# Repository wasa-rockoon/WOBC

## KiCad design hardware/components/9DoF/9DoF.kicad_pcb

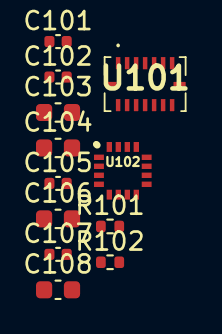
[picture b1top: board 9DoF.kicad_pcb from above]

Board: 2 copper layers, 12 parts (0 on the bottom side), 9 nets, no tracks yet.

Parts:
C101, C102, C107: 100nF; C_0402_1005Metric
C103, C104, C108: 10μF; C_0603_1608Metric
C105: 0.22μF; C_0402_1005Metric
C106: 4.7μF; C_0603_1608Metric
R101, R102: 4.7K; R_0402_1005Metric
U101: BMI088
U102: QMC5883L; _HMC5883L

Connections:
3V3: C101.1, C102.1, C103.1, C104.1, C107.1, C108.1, R101.2, R102.2, U101.3 (VDD), U101.7 (PS), U101.11 (VDDIO), U102.2 (VDD), U102.4 (S1), U102.13 (VDDIO)
AD0: R101.1, U101.15 (SDO1)
AD1: R102.1, U101.10 (SDO2)
GND: C101.2, C102.2, C103.2, C104.2, C106.2, C107.2, C108.2, U101.4 (GNDA), U101.6 (GNDIO), U102.9 (GND), U102.11 (GND)
unnamed: C106.1, U102.10 (C1)
unnamed: C105.1, U102.12 (SETC)
unnamed: C105.2, U102.8 (STEP)
SCL: U101.8 (SCL/SCK), U102.1 (SCL)
SDA: U101.9 (SDA/SDI), U102.16 (SDA)

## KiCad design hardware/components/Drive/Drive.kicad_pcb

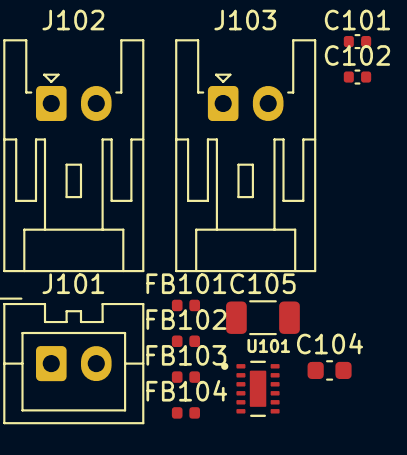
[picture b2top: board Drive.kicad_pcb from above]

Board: 2 copper layers, 12 parts (0 on the bottom side), 11 nets, no tracks yet.

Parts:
C101, C102: 100n; C_0402_1005Metric
C104: 10u; C_0603_1608Metric
C105: 100u; C_1206_3216Metric
FB101, FB102, FB103, FB104: FerriteBead; L_0402_1005Metric
J101: Conn_01x02_Pin; JST_XA_B02B-XASK-1_1x02_P2.50mm_Vertical
J102, J103: Conn_01x02_Pin; JST_XA_S02B-XASK-1N-BN_1x02_P2.50mm_Horizontal
U101: SON50P300X200X80-13N

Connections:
/VDD: C102.1, U101.12 (VCC)
AOUT1: FB101.1, U101.2 (AOUT1)
AOUT2: FB102.1, U101.3 (AOUT2)
BOUT1: FB103.1, U101.4 (BOUT1)
BOUT2: FB104.1, U101.5 (BOUT2)
GND: C101.2, C102.2, C104.2, C105.2, J101.2, U101.6 (GND), U101.11 (MODE), U101.13 (GND)
unnamed: C101.1, C104.1, C105.1, J101.1, U101.1 (VM)
unnamed: FB101.2, J102.1
unnamed: FB102.2, J102.2
unnamed: FB103.2, J103.1
unnamed: FB104.2, J103.2

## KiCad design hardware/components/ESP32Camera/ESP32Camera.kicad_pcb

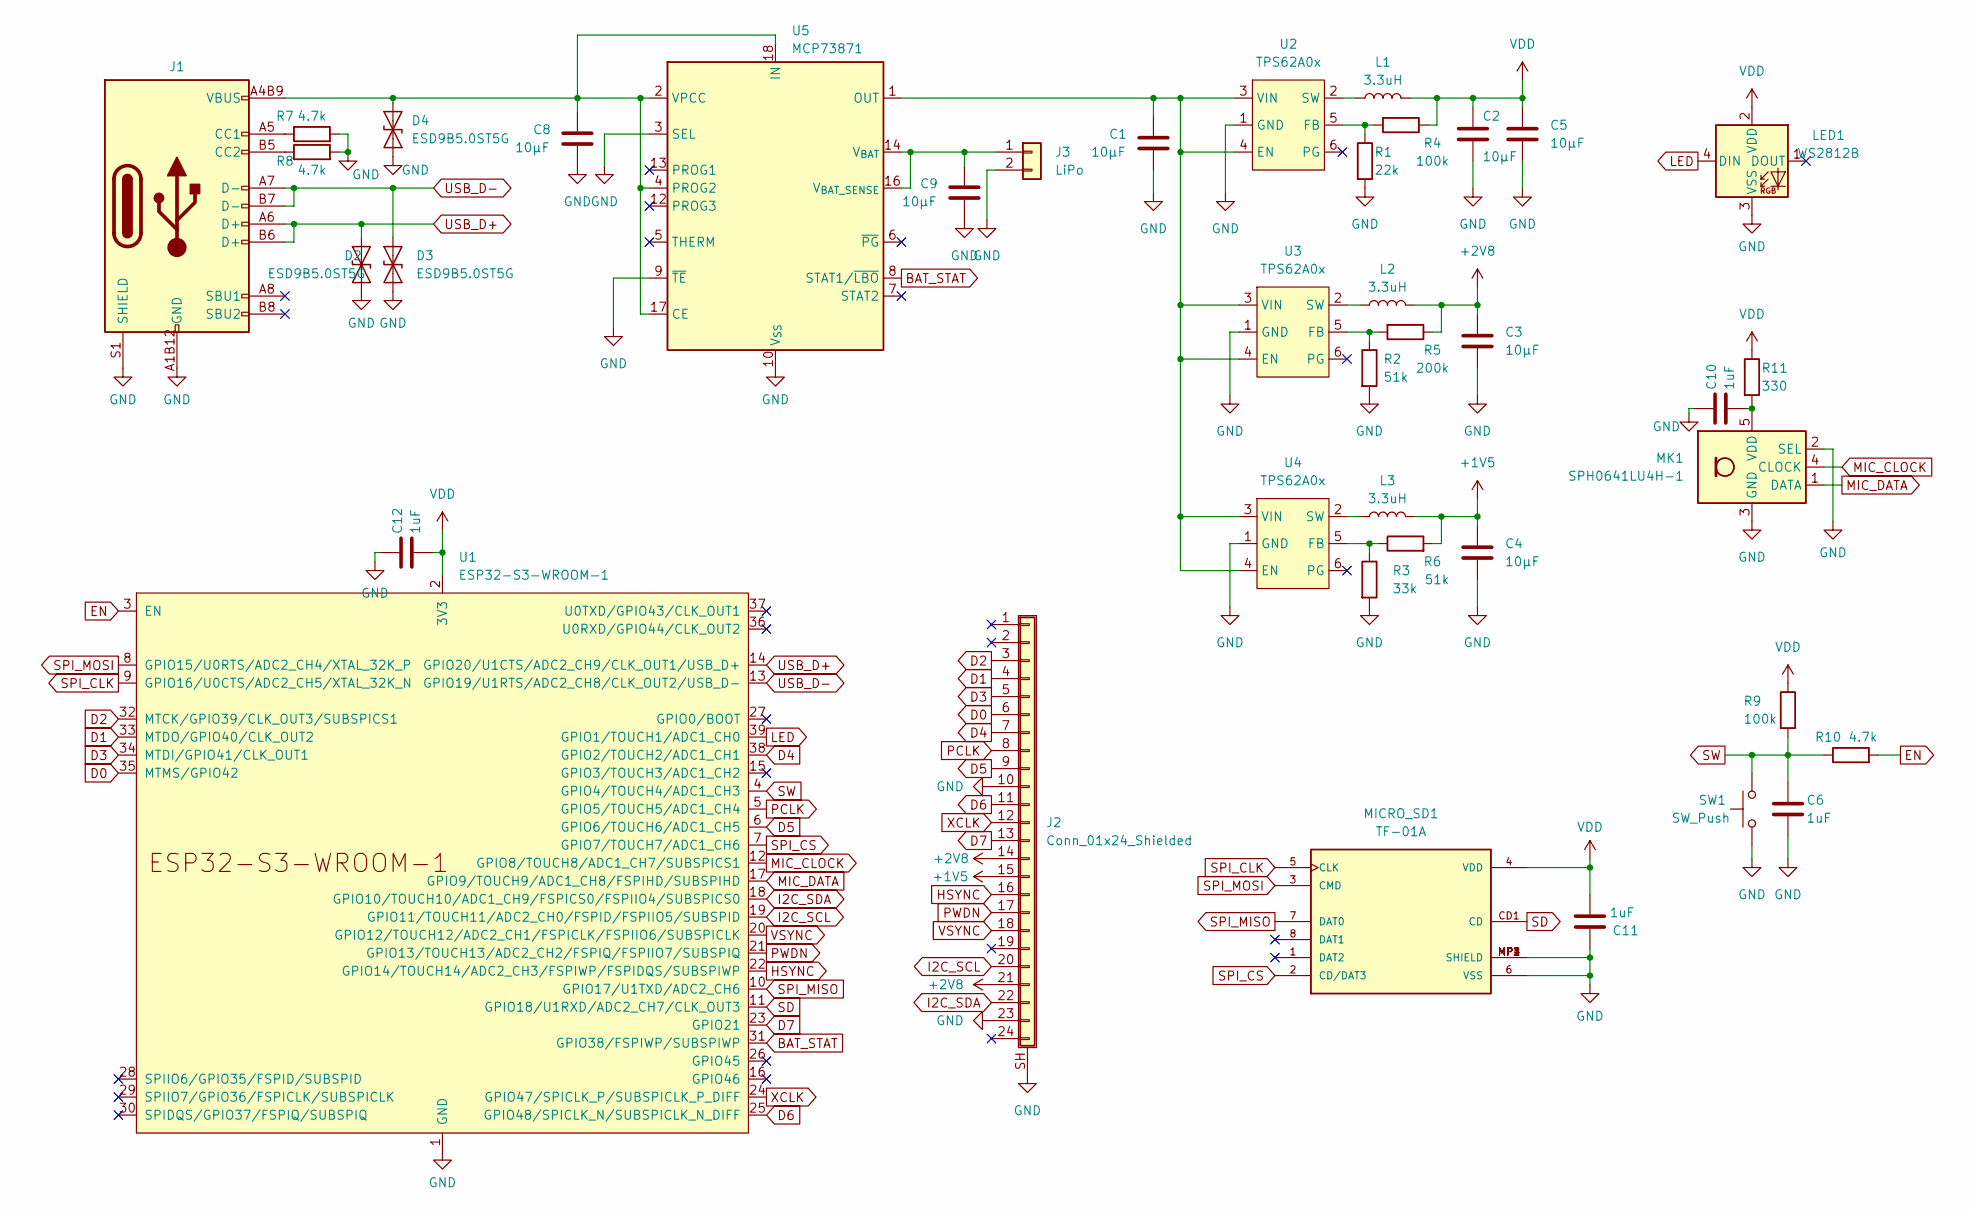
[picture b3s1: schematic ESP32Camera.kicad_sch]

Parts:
C1, C2, C3, C4, C5, C8, C9: 10µF; C_0603_1608Metric
C6, C10, C11, C12: 1uF; C_0402_1005Metric
D2, D3, D4: ESD9B5.0ST5G; D_SOD-523
J1: TYPE-C 16PFS 2JCB0.8-H7.45 IPX8; USB-C-SMD_SHOUHAN_TYPE-C-16PFS-2JCB0.8-H7.45
J2: Conn_01x24_Shielded; FPC-SMD_24P-P0.50_HCTL_HC-FPC-05-10-24RLTAG
J3: LiPo; JST_PH_S2B-PH-K_1x02_P2.00mm_Horizontal
L1, L2, L3: 3.3uH; L_Murata_DFE201610P
LED1: WS2812B; LED_XL-1615RGBC-WS2812B
MICRO_SD1: TF-01A
MK1: SPH0641LU4H-1; Knowles_LGA-5_3.5x2.65mm
R1: 22k; R_0402_1005Metric
R2, R6: 51k; R_0402_1005Metric
R3: 33k; R_0402_1005Metric
R4, R9: 100k; R_0402_1005Metric
R5: 200k; R_0402_1005Metric
R7, R8, R10: 4.7k; R_0402_1005Metric
R11: 330; R_0402_1005Metric
SW1: SW_Push; TVAF06-A020B-R
U1: ESP32-S3-WROOM-1
U2, U3, U4: TPS62A0x; SOT-563
U5: MCP73871; QFN-20-1EP_4x4mm_P0.5mm_EP2.5x2.5mm

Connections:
+1V5: C4.1, J2.15, L3.2, R6.2
+2V8: C3.1, J2.14, J2.21, L2.2, R5.1
BAT_STAT: U1.31 (GPIO38/FSPIWP/SUBSPIWP), U5.8 (STAT1/~LBO)
D0: J2.6, U1.35 (MTMS/GPIO42)
D1: J2.4, U1.33 (MTDO/GPIO40/CLK_OUT2)
D2: J2.3, U1.32 (MTCK/GPIO39/CLK_OUT3/SUBSPICS1)
D3: J2.5, U1.34 (MTDI/GPIO41/CLK_OUT1)
D4: J2.7, U1.38 (GPIO2/TOUCH2/ADC1_CH1)
D5: J2.9, U1.6 (GPIO6/TOUCH6/ADC1_CH5)
D6: J2.11, U1.25 (GPIO48/SPICLK_N/SUBSPICLK_N_DIFF)
D7: J2.13, U1.23 (GPIO21)
EN: R10.2, U1.3 (EN)
GND: C1.2, C2.2, C3.2, C4.2, C5.2, C6.2, C8.2, C9.2, C10.1, C11.1, C12.1, D2.1 (A1), D3.1 (A1), D4.1 (A1), J1.A1B12 (GND), J1.A12B1 (GND), J1.S1 (SHIELD), J1.S2 (SHIELD), J2.10, J2.23, J2.SH (Shield), J3.2, LED1.3 (VSS), MICRO_SD1.6 (VSS), MICRO_SD1.MP1 (SHIELD), MICRO_SD1.MP2 (SHIELD), MICRO_SD1.MP3 (SHIELD), MICRO_SD1.MP4 (SHIELD), MK1.2 (SEL), MK1.3 (GND), R1.2, R2.2, R3.2, R7.2, R8.2, SW1.1, U1.1 (GND), U1.40 (GND), U1.41 (GND), U2.1 (GND), U3.1 (GND), U4.1 (GND), U5.3 (SEL), U5.9 (~TE), U5.10 (V_{SS}), U5.11 (V_{SS}), U5.21 (V_{SS})
HSYNC: J2.16, U1.22 (GPIO14/TOUCH14/ADC2_CH3/FSPIWP/FSPIDQS/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)
I2C_SCL: J2.20, U1.19 (GPIO11/TOUCH11/ADC2_CH0/FSPID/FSPIIO5/S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)
I2C_SDA: J2.22, U1.18 (GPIO10/TOUCH10/ADC1_CH9/FSPICS0/FSPIIO4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)
LED: LED1.4 (DIN), U1.39 (GPIO1/TOUCH1/ADC1_CH0)
MIC_CLOCK: MK1.4 (CLOCK), U1.12 (GPIO8/TOUCH8/ADC1_CH7/SUBSPICS1)
MIC_DATA: MK1.1 (DATA), U1.17 (GPIO9/TOUCH9/ADC1_CH8/FSPIHD/SUBSPIHD)
unnamed: C8.1, D4.2 (A2), J1.A4B9 (VBUS), J1.A9B4 (VBUS), U5.2 (VPCC), U5.4 (PROG2), U5.17 (CE), U5.18 (IN), U5.19 (IN)
unnamed: J1.A5 (CC1), R7.1
unnamed: J1.B5 (CC2), R8.1
unnamed: C9.1, J3.1, U5.14 (V_{BAT}), U5.15 (V_{BAT}), U5.16 (V_{BAT_SENSE})
unnamed: C10.2, MK1.5 (VDD), R11.2
unnamed: C1.1, U2.3 (VIN), U2.4 (EN), U3.3 (VIN), U3.4 (EN), U4.3 (VIN), U4.4 (EN), U5.1 (OUT), U5.20 (OUT)
unnamed: R1.1, R4.2, U2.5 (FB)
unnamed: L1.1, U2.2 (SW)
unnamed: R2.1, R5.2, U3.5 (FB)
unnamed: L2.1, U3.2 (SW)
unnamed: R3.1, R6.1, U4.5 (FB)
unnamed: L3.1, U4.2 (SW)
PCLK: J2.8, U1.5 (GPIO5/TOUCH5/ADC1_CH4)
PWDN: J2.17, U1.21 (GPIO13/TOUCH13/ADC2_CH2/FSPIQ/FSPIIO7/S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)
SD: MICRO_SD1.CD1 (CD), U1.11 (GPIO18/U1RXD/ADC2_CH7/CLK_OUT3)
SPI_CLK: MICRO_SD1.5 (CLK), U1.9 (GPIO16/U0CTS/ADC2_CH5/XTAL_32K_N)
SPI_CS: MICRO_SD1.2 (CD/DAT3), U1.7 (GPIO7/TOUCH7/ADC1_CH6)
SPI_MISO: MICRO_SD1.7 (DAT0), U1.10 (GPIO17/U1TXD/ADC2_CH6)
SPI_MOSI: MICRO_SD1.3 (CMD), U1.8 (GPIO15/U0RTS/ADC2_CH4/XTAL_32K_P)
SW: C6.1, R9.2, R10.1, SW1.2, U1.4 (GPIO4/TOUCH4/ADC1_CH3)
USB_D+: D2.2 (A2), J1.A6 (D+), J1.B6 (D+), U1.14 (GPIO20/U1CTS/ADC2_CH9/CLK_OUT1/USB_D+)
USB_D-: D3.2 (A2), J1.A7 (D-), J1.B7 (D-), U1.13 (GPIO19/U1RTS/ADC2_CH8/CLK_OUT2/USB_D-)
VDD: C2.1, C5.1, C11.2, C12.2, L1.2, LED1.2 (VDD), MICRO_SD1.4 (VDD), R4.1, R9.1, R11.1, U1.2 (3V3)
VSYNC: J2.18, U1.20 (GPIO12/TOUCH12/ADC2_CH1/FSPICLK/FSPIIO6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)
XCLK: J2.12, U1.24 (GPIO47/SPICLK_P/SUBSPICLK_P_DIFF)

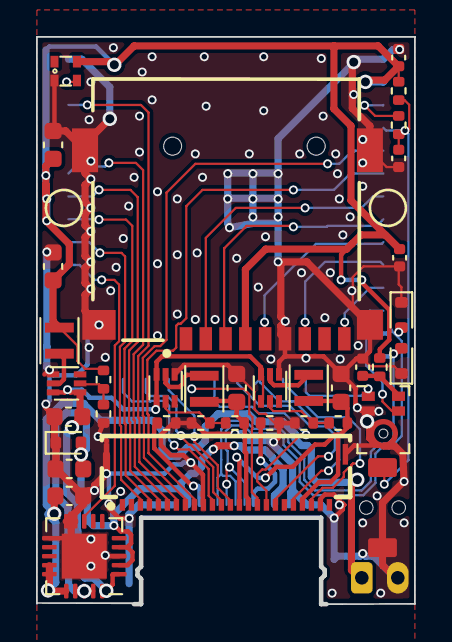
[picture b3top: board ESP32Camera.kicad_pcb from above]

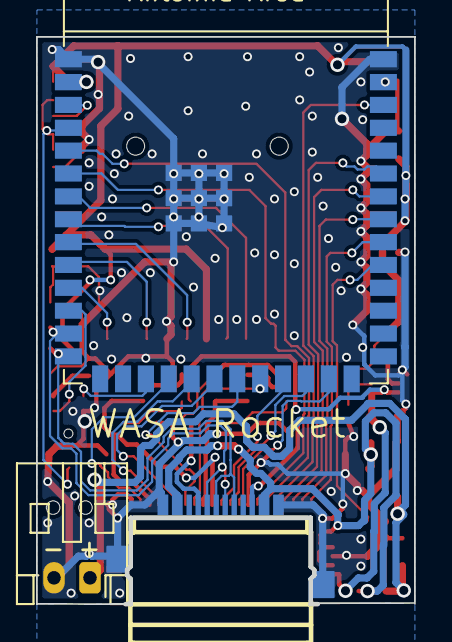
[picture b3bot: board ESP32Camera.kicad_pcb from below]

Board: 2 copper layers, 21.0 x 31.5 mm, 40 parts (3 on the bottom side), 44 nets.

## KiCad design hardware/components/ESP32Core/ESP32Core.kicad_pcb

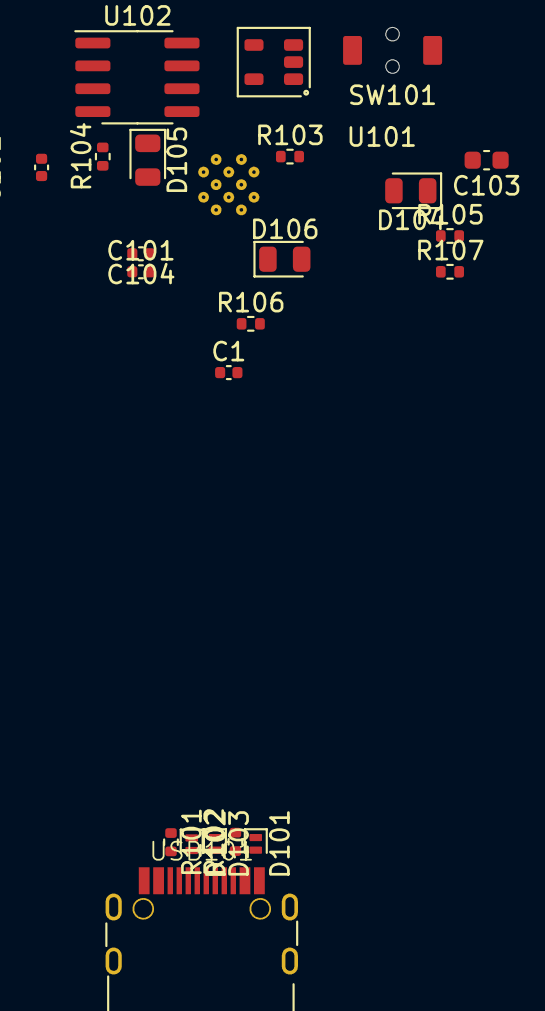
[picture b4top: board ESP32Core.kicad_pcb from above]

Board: 2 copper layers, 23 parts (1 on the bottom side), 19 nets, no tracks yet.

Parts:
C1: 10uF; C_0402_1005Metric
C101, C102, C104: 100nF; C_0402_1005Metric
C103: 10uF; C_0603_1608Metric
D101, D102, D103: 5V; D_SOD-882
D104: RESET; LED_0805_2012Metric
D105: ERROR; LED_0805_2012Metric
D106: STAT; LED_0805_2012Metric
R101, R102: 5.1k; R_0402_1005Metric
R103, R104, R106: 470; R_0402_1005Metric
R105, R107: 10k; R_0402_1005Metric
SW101: RESET_sw; TVAF06-A020B-R
U101: TPS3820; SOT-23-5
U102: SN65HVD230; SOIC-8_3.9x4.9mm_P1.27mm
U103: ESP32-S3-WROOM-1
USB101: USB_C_Receptacle_USB2.0; USB_C_TYPEC-301S-ACP16X7

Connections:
/CAN_RX: U102.4 (R), U103.36 (U0RXD/GPIO44/CLK_OUT2)
/CAN_TX: U102.1 (D), U103.37 (U0TXD/GPIO43/CLK_OUT1)
/I2C_SCL: R105.2, U103.9 (GPIO16/U0CTS/ADC2_CH5/XTAL_32K_N)
/I2C_SDA: R107.2, U103.10 (GPIO17/U1TXD/ADC2_CH6)
/USB_D+: D102.2 (A2), U103.14 (GPIO20/U1CTS/ADC2_CH9/CLK_OUT1/USB_D+), USB101.A6 (D+), USB101.B6 (D+)
/USB_D-: D103.2 (A2), U103.13 (GPIO19/U1RTS/ADC2_CH8/CLK_OUT2/USB_D-), USB101.A7 (D-), USB101.B7 (D-)
/VUSB: D101.2 (A2), USB101.A4 (VBUS), USB101.A9 (VBUS), USB101.B4 (VBUS), USB101.B9 (VBUS)
/WDI: U101.4 (WDI), U103.8 (GPIO15/U0RTS/ADC2_CH4/XTAL_32K_P)
GND: C1.2, C101.1, C102.1, C103.1, C104.2, D101.1 (A1), D102.1 (A1), D103.1 (A1), D105.1 (K), D106.1 (K), R101.2, R102.2, SW101.2, U101.2 (GND), U102.2 (GND), U102.8 (Rs), U103.1 (GND), U103.40 (GND), U103.41 (GND), USB101.A1 (GND), USB101.A12 (GND), USB101.B1 (GND), USB101.B12 (GND), USB101.S1 (SHIELD)
unnamed: D104.2 (A), R103.2
unnamed: D105.2 (A), R104.2
unnamed: D106.2 (A), R106.2
unnamed: SW101.1, U101.3 (MR)
unnamed: R104.1, U103.34 (MTDI/GPIO41/CLK_OUT1)
unnamed: R106.1, U103.35 (MTMS/GPIO42)
unnamed: R101.1, USB101.A5 (CC1)
unnamed: R102.1, USB101.B5 (CC2)
RESET: D104.1 (K), U101.1 (RESET), U103.3 (EN)
VDD: C1.1, C101.2, C102.2, C103.2, C104.1, R103.1, R105.1, R107.1, U101.5 (VDD), U102.3 (VCC), U103.2 (3V3)

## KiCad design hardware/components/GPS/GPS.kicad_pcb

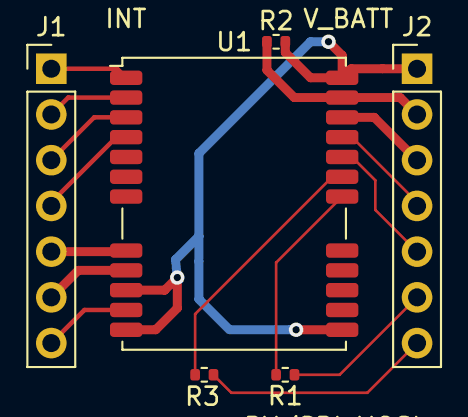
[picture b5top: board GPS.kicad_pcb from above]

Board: 2 copper layers, 6 parts (0 on the bottom side), 16 nets.

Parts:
J1, J2: Conn_01x07_Pin; PinHeader_1x07_P2.54mm_Vertical
R1, R3: R; R_0402_1005Metric
R2: 100K; R_0402_1005Metric
U1: NEO-M9N; ublox_NEO

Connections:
3V3: J2.2, R2.1, U1.23 (VCC)
D_SEL: J1.2, U1.2 (D_SEL)
GND: J2.1, R2.2, U1.10 (GND), U1.12 (GND), U1.13 (GND), U1.24 (GND)
GPS_ANT1: J1.7, U1.11 (RF_IN)
INT: J1.4, U1.4 (EXTINT)
unnamed: R3.1, U1.19 (SCL/SPI_CLK)
unnamed: R1.2, U1.18 (SDA/~SPI_CS)
PRS: J1.3, U1.3 (TIMEPULSE)
RESET: J1.5, U1.8 (~RESET)
RX/SPI_MOSI: J2.4, U1.21 (RXD/SPI_MOSI)
SAFE: J1.1, U1.1 (~SAFEBOOT)
SCL/SCK: J2.7, R3.2
SDA/CS: J2.6, R1.1
TX/SPI_MISO: J2.5, U1.20 (TXD/SPI_MISO)
VCC_RF: J1.6, U1.9 (VCC_RF)
V_BATT: J2.3, U1.22 (V_BCKP)

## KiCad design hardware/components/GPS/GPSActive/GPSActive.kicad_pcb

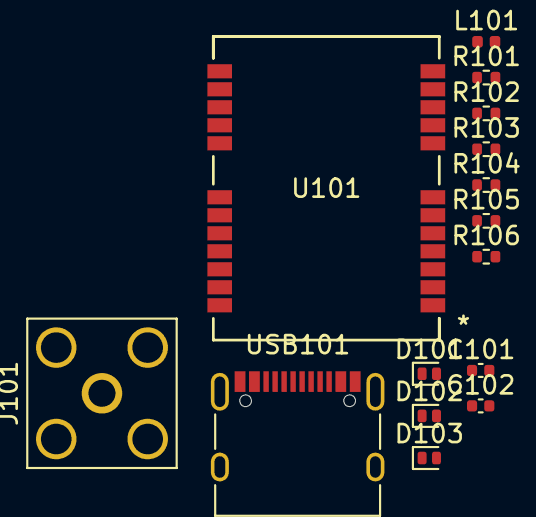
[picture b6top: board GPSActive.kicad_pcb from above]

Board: 2 copper layers, 15 parts (0 on the bottom side), 11 nets, no tracks yet.

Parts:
C101, C102: 100nF; C_0402_1005Metric
D101, D102, D103: 5V; D_SOD-882D
J101: SMA; SMA_Amphenol_132203-12_Horizontal
L101: 27nH, 300mA; L_0402_1005Metric
R101, R102: 5.1k; R_0402_1005Metric
R103: 10; R_0402_1005Metric
R104, R105: 33; R_0402_1005Metric
R106: 100K; R_0402_1005Metric
U101: NEO-M9N-00B; SMT_9N-00B_UBL
USB101: USB_C_Receptacle_USB2.0; USB_C_Receptacle_XKB_U262-16XN-4BVC11

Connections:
/USB_D+: D102.2 (A2), U101.6 (USB_DP), USB101.A6 (D+), USB101.B6 (D+)
/USB_D-: D103.2 (A2), U101.5 (USB_DM), USB101.A7 (D-), USB101.B7 (D-)
GND: C101.2, C102.1, D101.1 (A1), D102.1 (A1), D103.1 (A1), J101.2 (Ext), R101.2, R102.2, R106.2, U101.10 (GND), U101.12 (GND), U101.13 (GND), U101.24 (GND), USB101.A1 (GND), USB101.A12 (GND), USB101.B1 (GND), USB101.B12 (GND), USB101.S1 (SHIELD)
GPS_ANT1: J101.1 (In), L101.1
unnamed: C101.1, L101.2, R103.2
unnamed: D101.2 (A2), USB101.A4 (VBUS), USB101.A9 (VBUS), USB101.B4 (VBUS), USB101.B9 (VBUS)
unnamed: R104.2, U101.21 (RXD_/_SPI_MOSI)
unnamed: R105.2, U101.20 (TXD_/_SPI_MISO)
unnamed: R101.1, USB101.A5 (CC1)
unnamed: R102.1, USB101.B5 (CC2)
VDD: C102.2, U101.7 (V_USB), U101.23 (VCC)

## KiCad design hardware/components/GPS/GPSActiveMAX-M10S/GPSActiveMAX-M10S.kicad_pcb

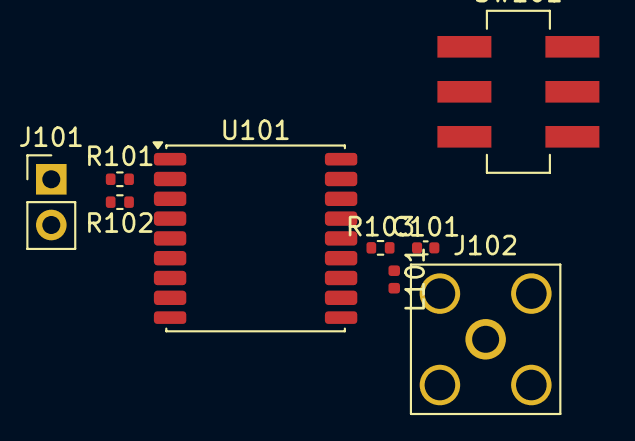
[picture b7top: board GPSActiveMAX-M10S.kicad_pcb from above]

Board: 2 copper layers, 9 parts (0 on the bottom side), 10 nets, no tracks yet.

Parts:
C101: 10nF; C_0402_1005Metric
J101: Conn_01x02; PinHeader_1x02_P2.54mm_Vertical
J102: SMA; SMA_Amphenol_132203-12_Horizontal
L101: 27nH, 300mA; L_0402_1005Metric
R101, R102: 33; R_0402_1005Metric
R103: 10; R_0402_1005Metric
SW101: SW_Push_DPDT; IS-2245S-G
U101: MAX-M10S; ublox_MAX

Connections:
GND: C101.2, J102.2 (Ext), U101.1 (GND), U101.10 (GND), U101.12 (GND)
unnamed: C101.1, L101.1, R103.2
unnamed: J101.2, SW101.4 (A)
unnamed: J102.1 (In), L101.2, U101.11 (RF_IN)
unnamed: R101.2, SW101.2 (B)
unnamed: R102.2, SW101.5 (B)
unnamed: R102.1, U101.3 (RXD)
unnamed: R101.1, U101.2 (TXD)
unnamed: R103.1, U101.14 (VCC_RF)
VDD: U101.7 (VCC_IO), U101.8 (VCC)
